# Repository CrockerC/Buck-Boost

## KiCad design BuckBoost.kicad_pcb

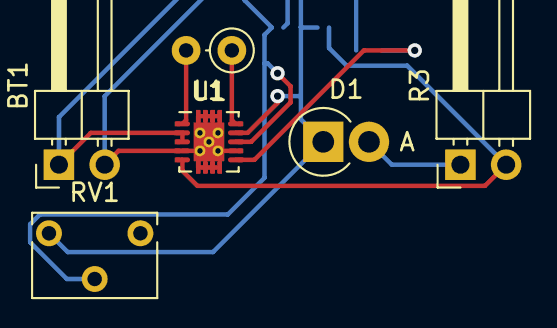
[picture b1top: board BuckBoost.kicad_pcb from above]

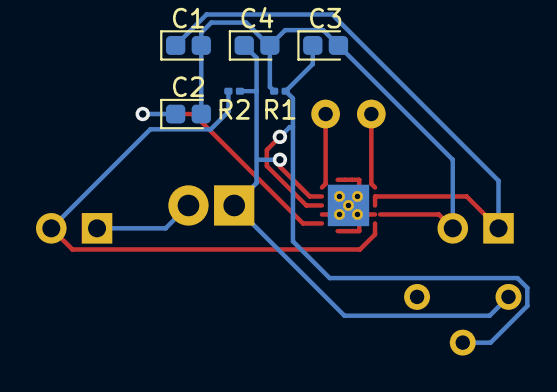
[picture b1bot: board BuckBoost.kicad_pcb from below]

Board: 2 copper layers, 12 parts (6 on the bottom side), 9 nets.

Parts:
BT1: Vin; PinHeader_1x02_P2.54mm_Horizontal
C1: 20uF; CP_EIA-1608-08_AVX-J
C2: .1uF; CP_EIA-1608-08_AVX-J
C3: 10pF; CP_EIA-1608-08_AVX-J
C4: 66uF; CP_EIA-1608-08_AVX-J
D1: DIODE; D_DO-15_P2.54mm_Vertical_AnodeUp
L1: 1uH; L_Axial_L5.3mm_D2.2mm_P2.54mm_Vertical_Vishay_IM-1
R1: 111k; R_0201_0603Metric
R2: 1M; R_0201_0603Metric
R3: Vout; PinHeader_1x02_P2.54mm_Horizontal
RV1: R_POT; Potentiometer_Bourns_3266W_Vertical
U1: TPS63060; Texas_S-PWSON-N10_ThermalVias

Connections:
unnamed: BT1.1, C1.1, U1.2, U1.3
unnamed: BT1.2, C1.2, C2.2, C3.2, C4.2, R1.2, U1.4, U1.7, U1.11
unnamed: C2.1, U1.6
unnamed: C3.1, R1.1, RV1.2, U1.8
unnamed: C4.1, D1.1, R2.1, RV1.3, U1.9
unnamed: D1.2, R3.1
unnamed: L1.1, U1.10
unnamed: L1.2, U1.1
unnamed: R2.2, R3.2, U1.5
